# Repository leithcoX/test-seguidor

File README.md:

# Robot Seguidor de Línea

Test de seguidor de línea para competiciones.
Nombre pendiente.

## Estructura del proyecto
Boceto de la estructura del proyecto

```bash
.
├── placa_sensor
│   ├── kicad_sch
│   └── kicad_pcb
├── placa_seguidor
│   ├── kicad_sch
│   └── kicad_pcb
├── modelo
│   └── seguidor.FCStd
├── include
│   ├── file1.h
│   └── file2.h
├── src
│   ├── file1.ino
│   └── file2.ino
├── res
│   ├── datasheets.pdf
│   ├── images.png
│   └── referencias o links
└── README.md
```

## Requisitos
 - 20cm largo x 14cm de ancho x 10cm de alto
 - Area mínima de 23mm x 14mm. Visible. No pueden ser secciones de la batería.
 - No control remoto, o que solo de la orden de salida
 - Indicador luminoso (fijo o intermitente) que muestra cuando el robot inicia a correr.
 - Ruedas sin adherentes

## TODOs
 - ~~Rediseñar la placa de sensores (corregir errores) y mandar al lci~~
 - ~~Puente H~~
 - ~~Arduino Nano o ATmega328~~ y programarlo
 - ~~Comprar Placa Experimental~~
 - Elegir batería
 - Hacer un diagrama tal vez de como seguir el proyecto
 - ~~Hacér una bitácora~~ (subirla al repo?)
 - Agregar vista general del proyecto desde la página principal
 - ~~Agregar una lista de compras que puedan editar todos~~
 - Terminar de Soldar/limpiar modulo de sensores chequeando continuidad (Ciin lo hace el jueves)
 - Probar modulo se sensores con arduino (Armar código de prueba) 
 - 

## Artículos pendientes
 - 2 Capacitores 100nf (Puente H)
 - 10 x Diodos 1N4007  (Puente H)
 - 1 x Zócalo ZT16A (Zocalo 16 pines para puente H)

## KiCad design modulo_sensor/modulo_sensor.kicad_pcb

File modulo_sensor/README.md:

# Modulo de sensores

Este módulo se encarga de la lectura de la línea.

[comment]: Hacer_alguna_descripción_más

Vista previa de la PCB desde arriba

Vista previa de la PCB desde abajo

## TODOs
En orden de prioridad
- ~~Automatizar exportar los archivos de fabricación~~
- Hacer las pistas más grandes si es posible
- El script debe exportar a PDF ambos lados en la misma hoja conservando las dimensiones para imprimir el circuito.
- ~~Exportar a otros formatos (SVG, STEP, etc)~~
- Agregar alguna compatibilidad para Windows(?
- Agregar algun check para el momento de subir a Github
- Tal vez agregar algunas opciones para controlar el script(?
- Cambiar las rutas relativas con alguna variable de entorno(?

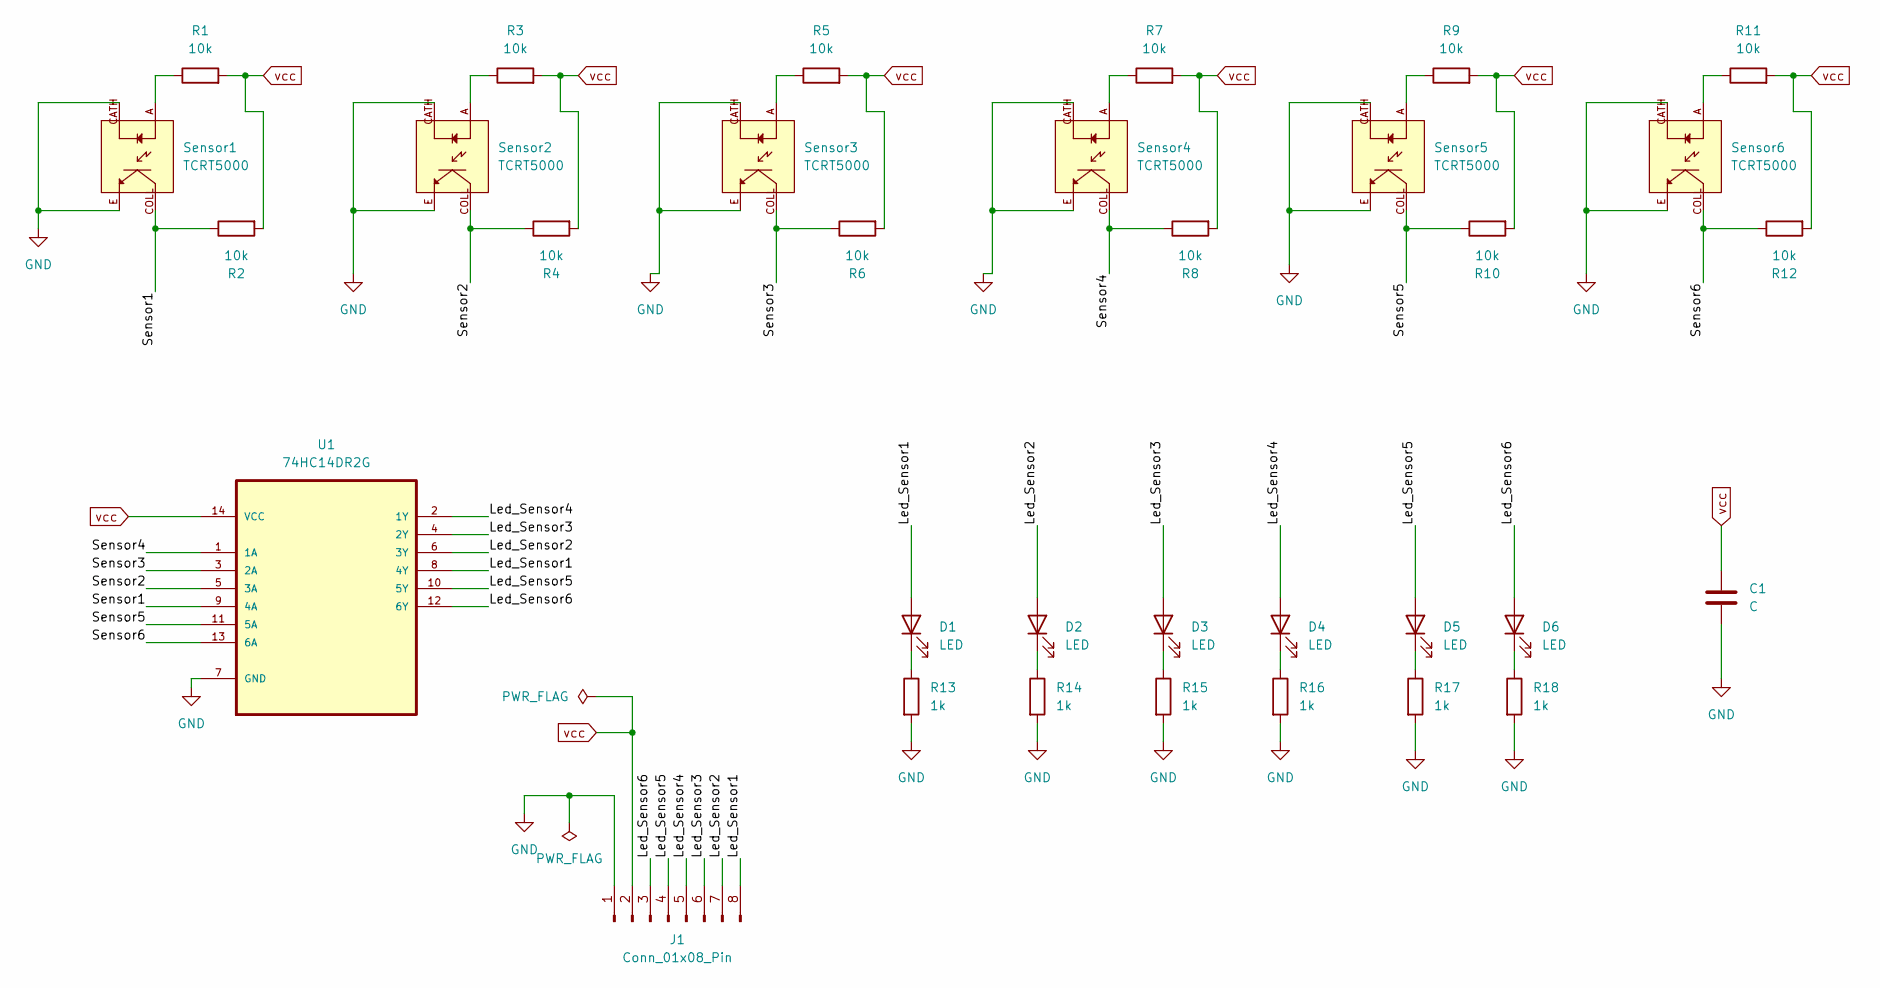
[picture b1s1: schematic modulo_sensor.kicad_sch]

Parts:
C1: C; C_Disc_D3.0mm_W1.6mm_P2.50mm
D1, D2, D3, D4, D5, D6: LED; LED_1206_3216Metric_Pad1.42x1.75mm_HandSolder
J1: Conn_01x08_Pin; PinHeader_1x08_P2.54mm_Horizontal
R1, R2, R3, R4, R5, R6, R7, R8, R9, R10, R11, R12: 10k; R_0805_2012Metric_Pad1.20x1.40mm_HandSolder
R13, R14, R15, R16, R17, R18: 1k; R_0805_2012Metric_Pad1.20x1.40mm_HandSolder
Sensor1, Sensor2, Sensor3, Sensor4, Sensor5, Sensor6: TCRT5000; OPTO_TCRT5000; PARTREV 1.7
U1: 74HC14DR2G; DIP-14_W7.62mm_Socket; MPN 74HC14DR2G

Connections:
/Led_Sensor1: D1.2 (A), J1.8, U1.8 (4Y)
/Led_Sensor2: D2.2 (A), J1.7, U1.6 (3Y)
/Led_Sensor3: D3.2 (A), J1.6, U1.4 (2Y)
/Led_Sensor4: D4.2 (A), J1.5, U1.2 (1Y)
/Led_Sensor5: D5.2 (A), J1.4, U1.10 (5Y)
/Led_Sensor6: D6.2 (A), J1.3, U1.12 (6Y)
/Sensor1: R2.1, Sensor1.COLL, U1.9 (4A)
/Sensor2: R4.1, Sensor2.COLL, U1.5 (3A)
/Sensor3: R6.1, Sensor3.COLL, U1.3 (2A)
/Sensor4: R8.1, Sensor4.COLL, U1.1 (1A)
/Sensor5: R10.1, Sensor5.COLL, U1.11 (5A)
/Sensor6: R12.1, Sensor6.COLL, U1.13 (6A)
GND: C1.2, J1.1, R13.2, R14.2, R15.2, R16.2, R17.2, R18.2, Sensor1.CATH, Sensor1.E, Sensor2.CATH, Sensor2.E, Sensor3.CATH, Sensor3.E, Sensor4.CATH, Sensor4.E, Sensor5.CATH, Sensor5.E, Sensor6.CATH, Sensor6.E, U1.7 (GND)
unnamed: D1.1 (K), R13.1
unnamed: D2.1 (K), R14.1
unnamed: D3.1 (K), R15.1
unnamed: D4.1 (K), R16.1
unnamed: D5.1 (K), R17.1
unnamed: D6.1 (K), R18.1
unnamed: R1.1, Sensor1.A
unnamed: R3.1, Sensor2.A
unnamed: R5.1, Sensor3.A
unnamed: R7.1, Sensor4.A
unnamed: R9.1, Sensor5.A
unnamed: R11.1, Sensor6.A
vcc: C1.1, J1.2, R1.2, R2.2, R3.2, R4.2, R5.2, R6.2, R7.2, R8.2, R9.2, R10.2, R11.2, R12.2, U1.14 (VCC)

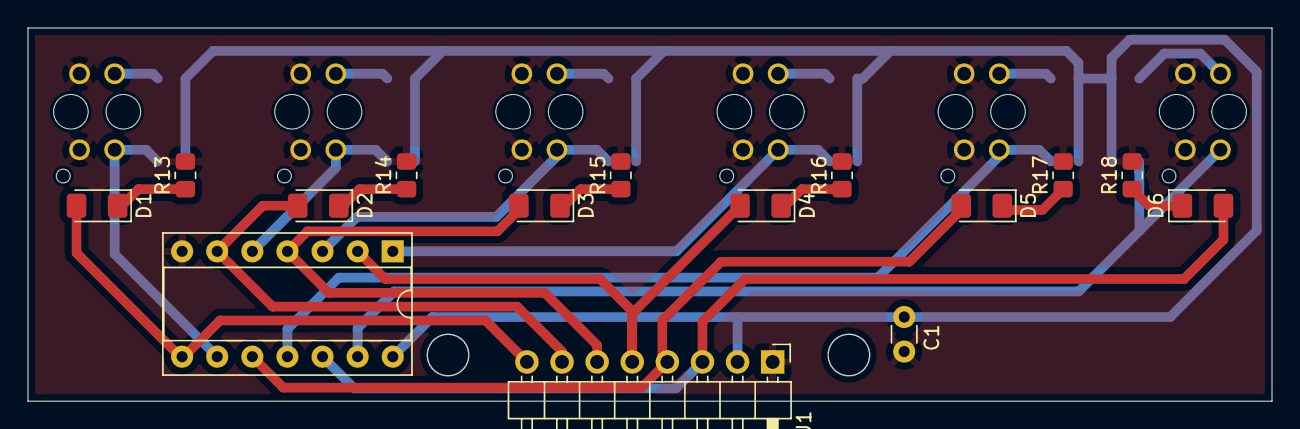
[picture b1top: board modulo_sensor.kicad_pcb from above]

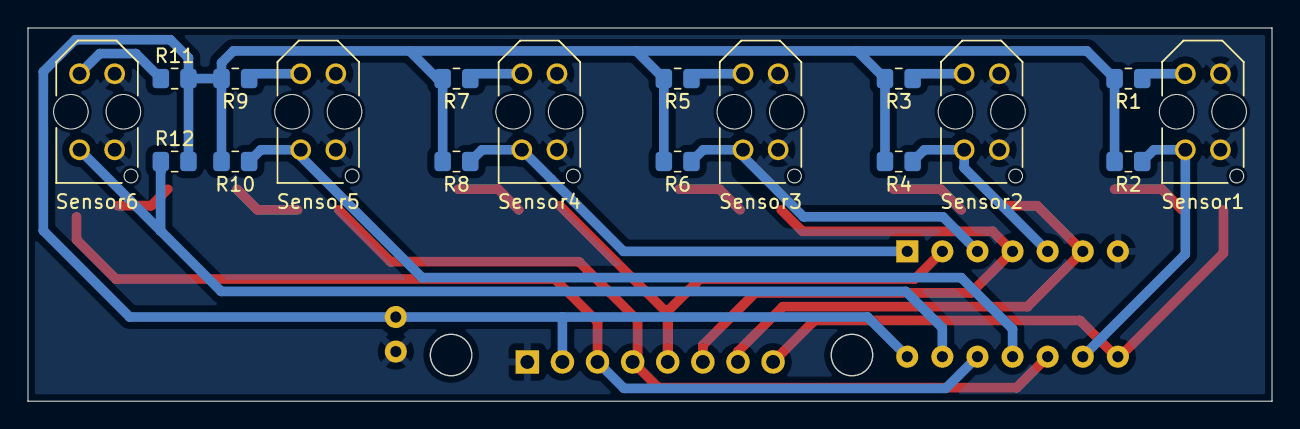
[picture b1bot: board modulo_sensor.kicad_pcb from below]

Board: 2 copper layers, 89.9 x 27.0 mm, 33 parts (18 on the bottom side), 26 nets.

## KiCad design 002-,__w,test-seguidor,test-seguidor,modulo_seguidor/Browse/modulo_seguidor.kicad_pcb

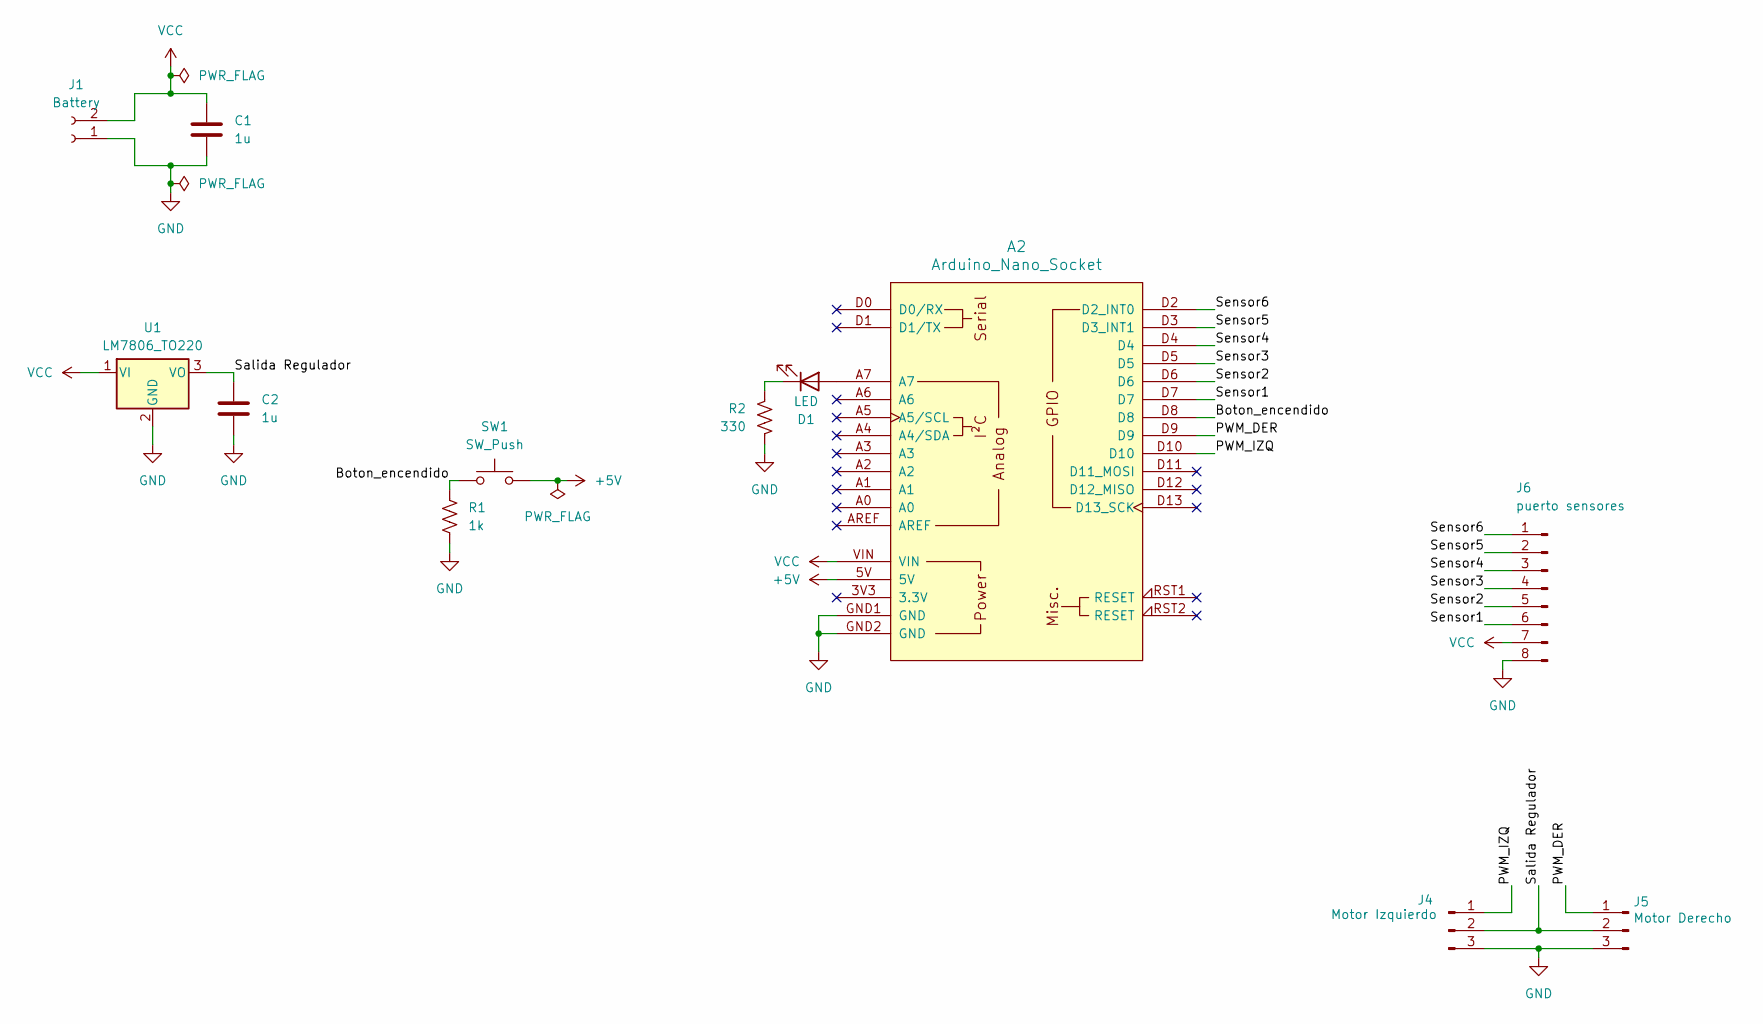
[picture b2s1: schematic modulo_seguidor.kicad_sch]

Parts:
A2: Arduino_Nano_Socket
C1, C2: 1u; C_Disc_D7.0mm_W2.5mm_P5.00mm
D1: LED; LED_D5.0mm
J1: Battery; Molex_KK-254_AE-6410-02A_1x02_P2.54mm_Vertical
J4: Motor Izquierdo; PinHeader_1x03_P2.54mm_Vertical
J5: Motor Derecho; PinHeader_1x03_P2.54mm_Vertical
J6: puerto sensores; PinHeader_1x08_P2.54mm_Horizontal
R1: 1k; R_Axial_DIN0411_L9.9mm_D3.6mm_P12.70mm_Horizontal
R2: 330; R_Axial_DIN0411_L9.9mm_D3.6mm_P12.70mm_Horizontal
SW1: SW_Push; SW_PUSH_6mm
U1: LM7806_TO220; TO-220-3_Vertical

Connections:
+5V: A2.5V, SW1.1
/Boton_encendido: A2.D8, R1.1, SW1.2
/PWM_DER: A2.D9, J5.1
/PWM_IZQ: A2.D10, J4.1
/Salida Regulador: C2.1, J4.2, J5.2, U1.3 (VO)
/Sensor1: A2.D7, J6.6
/Sensor2: A2.D6, J6.5
/Sensor3: A2.D5, J6.4
/Sensor4: A2.D4, J6.3
/Sensor5: A2.D3 (D3_INT1), J6.2
/Sensor6: A2.D2 (D2_INT0), J6.1
GND: A2.GND1 (GND), A2.GND2 (GND), C1.2, C2.2, J1.1, J4.3, J5.3, J6.8, R1.2, R2.2, U1.2 (GND)
unnamed: A2.A7, D1.2 (A)
unnamed: D1.1 (K), R2.1
VCC: A2.VIN, C1.1, J1.2, J6.7, U1.1 (VI)

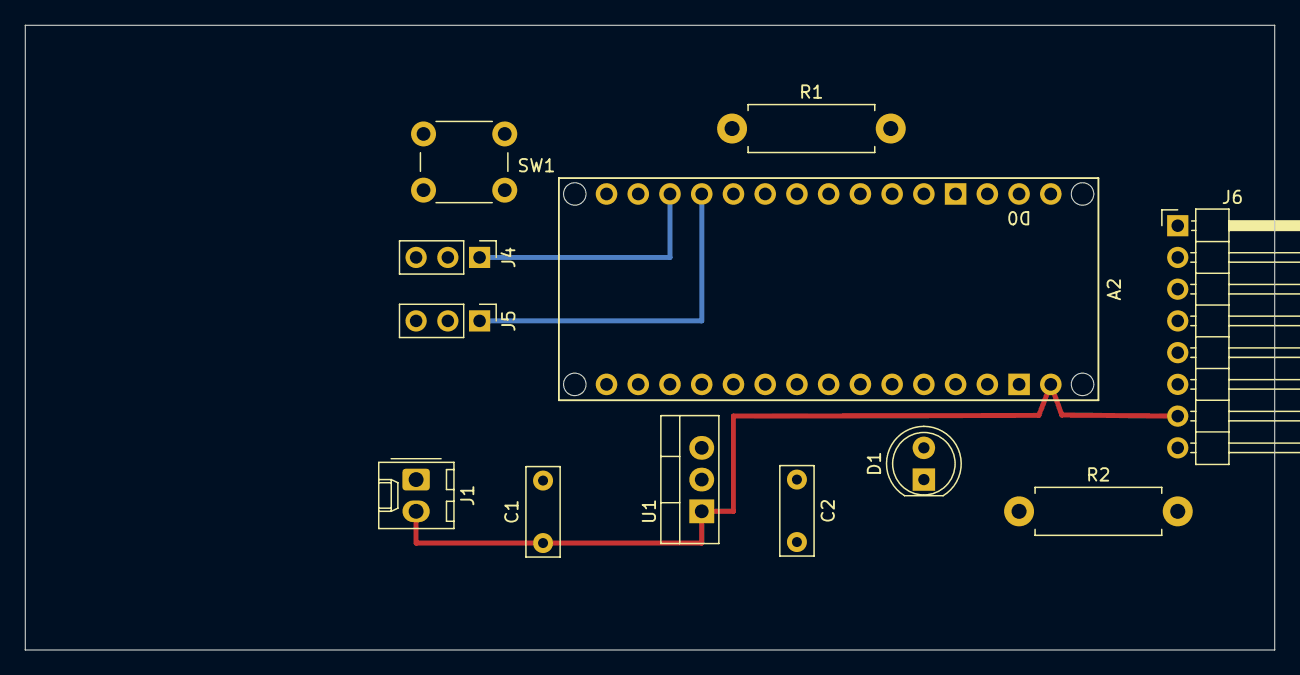
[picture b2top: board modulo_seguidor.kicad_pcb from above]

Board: 12 copper layers, 100.0 x 50.0 mm, 12 parts (0 on the bottom side), 15 nets.

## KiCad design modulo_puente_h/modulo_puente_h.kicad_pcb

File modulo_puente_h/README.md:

# Modulo Puente H

Este módulo se encarga de controlar los motores a partir de las entradas recibidas por sus pines.

Las pistas azules representan conexiones físicas cableadas por nosotros ya que el diseño no es posible en una placa simple faz.

## TODOs
 - [ ] Revisar las medidas de la placa
 - [ ] Hacer los agujeros para las medidas del modelo 3D
 - [ ] El regulador de tensión debería ir en este módulo?
 - [ ] Revisar las conexiones
 - [ ] Replantearse el diseño del puente h, ¿Qué tensión tienen los motores?

#### Nota

Considerar que se podría diseñar todo en la parte posterior y soldar los componentes del lado que no tiene cobre.

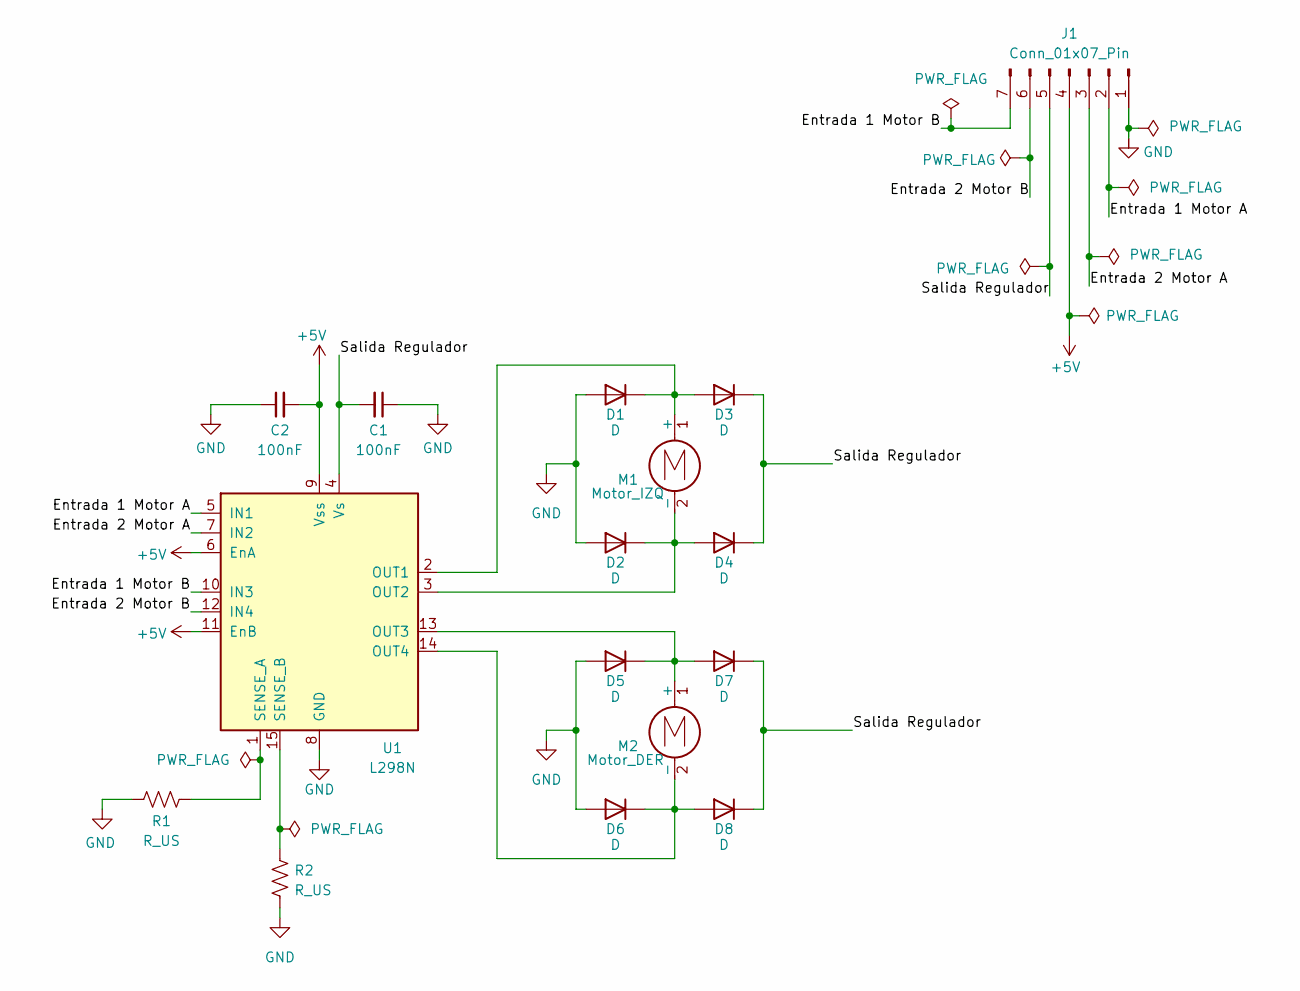
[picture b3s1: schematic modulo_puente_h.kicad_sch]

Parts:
C1, C2: 100nF; C_Disc_D7.0mm_W2.5mm_P5.00mm
D1, D2, D3, D4, D5, D6, D7, D8: D; D_DO-41_SOD81_P7.62mm_Horizontal
J1: Conn_01x07_Pin; PinHeader_1x07_P2.54mm_Vertical
M1: Motor_IZQ; R_Axial_DIN0207_L6.3mm_D2.5mm_P2.54mm_Vertical
M2: Motor_DER; R_Axial_DIN0207_L6.3mm_D2.5mm_P2.54mm_Vertical
R1, R2: R_US; R_0805_2012Metric_Pad1.20x1.40mm_HandSolder
U1: L298N; TO-220-15_P2.54x2.54mm_StaggerOdd_Lead4.58mm_Vertical

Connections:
+5V: C2.2, J1.4, U1.6 (EnA), U1.9 (Vss), U1.11 (EnB)
/Entrada 1 Motor A: J1.2, U1.5 (IN1)
/Entrada 1 Motor B: J1.7, U1.10 (IN3)
/Entrada 2 Motor A: J1.3, U1.7 (IN2)
/Entrada 2 Motor B: J1.6, U1.12 (IN4)
/Salida Regulador: C1.2, D3.1 (K), D4.1 (K), D7.1 (K), D8.1 (K), J1.5, U1.4 (Vs)
GND: C1.1, C2.1, D1.2 (A), D2.2 (A), D5.2 (A), D6.2 (A), J1.1, R1.2, R2.1, U1.8 (GND)
unnamed: D1.1 (K), D3.2 (A), M1.1 (+), U1.2 (OUT1)
unnamed: D2.1 (K), D4.2 (A), M1.2 (-), U1.3 (OUT2)
unnamed: D5.1 (K), D7.2 (A), M2.1 (+), U1.13 (OUT3)
unnamed: D6.1 (K), D8.2 (A), M2.2 (-), U1.14 (OUT4)
unnamed: R1.1, U1.1 (SENSE_A)
unnamed: R2.2, U1.15 (SENSE_B)

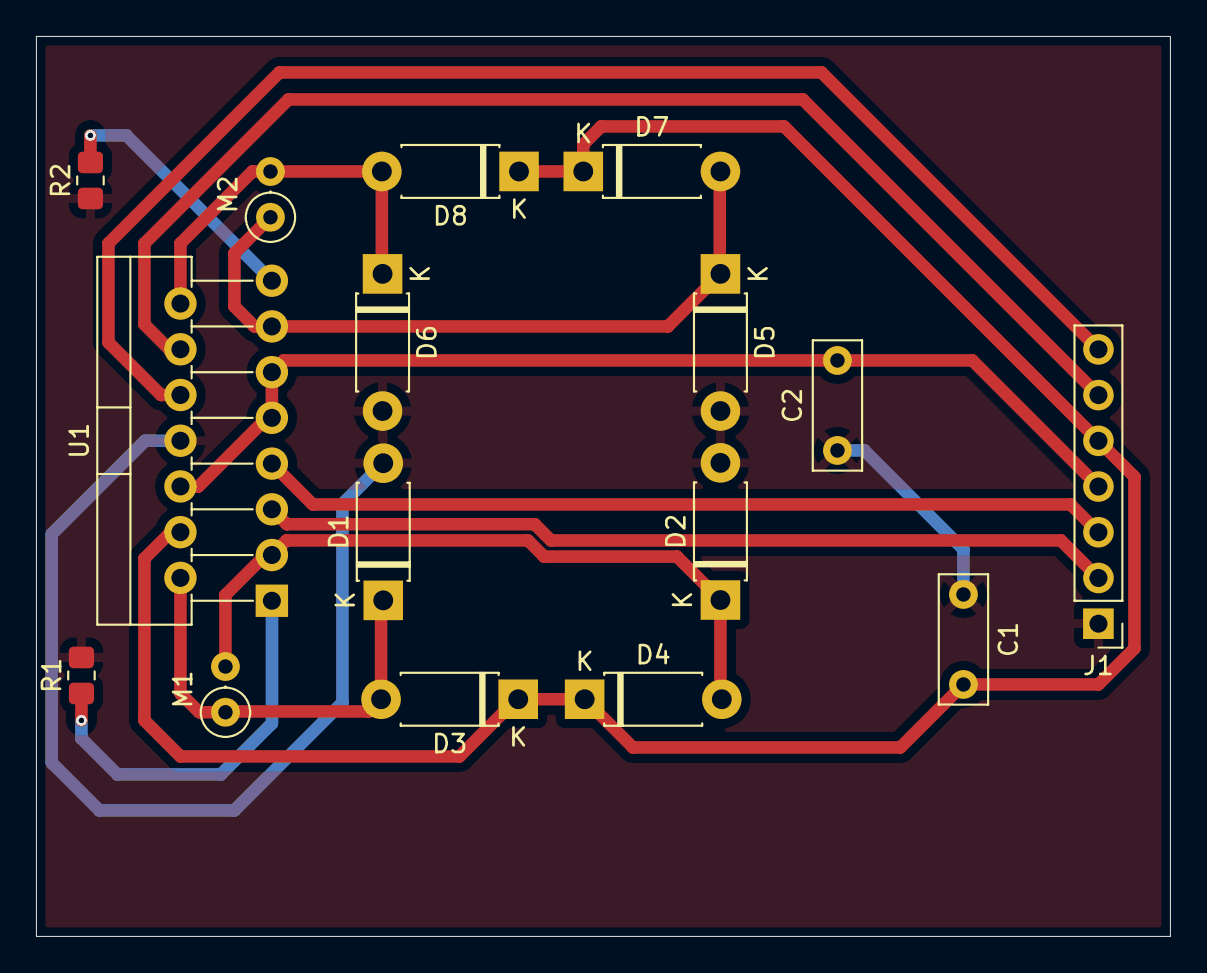
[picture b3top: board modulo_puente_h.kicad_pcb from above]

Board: 2 copper layers, 63.0 x 50.0 mm, 16 parts (0 on the bottom side), 13 nets.

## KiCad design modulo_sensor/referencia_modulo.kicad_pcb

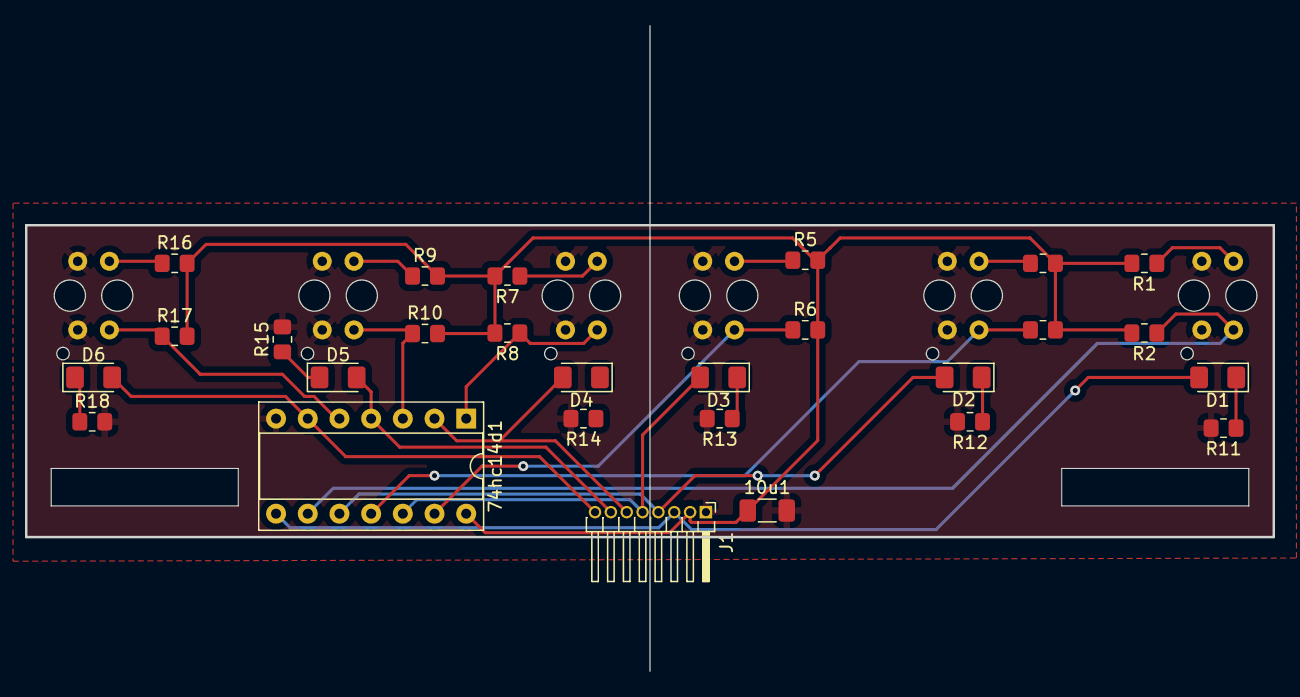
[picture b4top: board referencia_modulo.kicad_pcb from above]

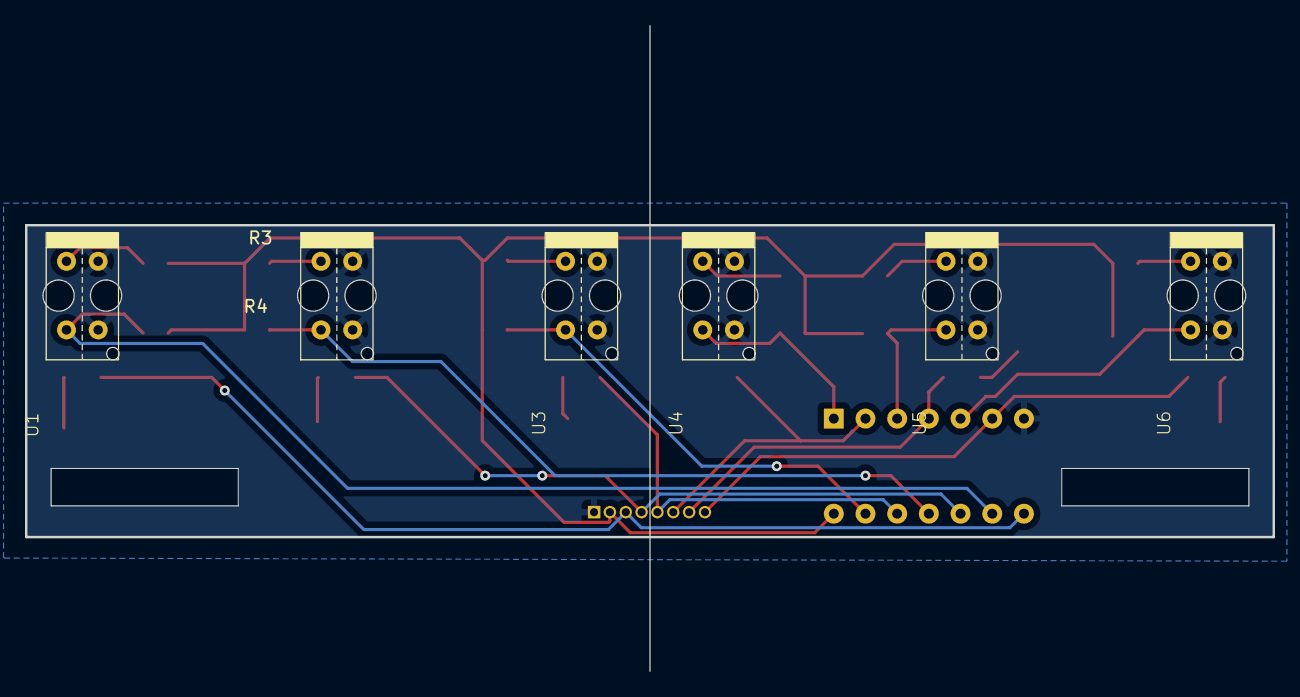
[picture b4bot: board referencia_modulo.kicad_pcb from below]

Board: 2 copper layers, 100.0 x 51.7 mm, 33 parts (6 on the bottom side), 26 nets.

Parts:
10u1: CAP; C_1206_3216Metric_Pad1.33x1.80mm_HandSolder
74hc14d1: A_14-LC-TT; DIP-14_W7.62mm_Socket
D1, D2, D3, D4, D5, D6: LED; LED_1206_3216Metric_Pad1.42x1.75mm_HandSolder
J1: Conn_01x08_Pin; PinHeader_1x08_P1.27mm_Horizontal
R1, R3, R5, R7, R9, R16: 220; R_0805_2012Metric_Pad1.20x1.40mm_HandSolder
R2, R4, R6, R8, R10, R17: 10k; R_0805_2012Metric_Pad1.20x1.40mm_HandSolder
R11, R12, R13, R14, R15, R18: 1k; R_0805_2012Metric_Pad1.20x1.40mm_HandSolder
U1, U2, U3, U4, U5, U6: TCMT4106; tcrt5000

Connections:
/sensor1: 74hc14d1.8, D1.2 (A), J1.3
/sensor1_unfiltered: 74hc14d1.9, R2.1, U1.16
/sensor2: 74hc14d1.10, D2.2 (A), J1.4
/sensor2_unfiltered: 74hc14d1.11, R4.1, U2.16
/sensor3: 74hc14d1.12, D3.2 (A), J1.5
/sensor3_unfiltered: 74hc14d1.13, R6.1, U3.16
/sensor4: 74hc14d1.2, D4.2 (A), J1.6
/sensor4_unfiltered: 74hc14d1.1, R8.1, U4.16
/sensor5: 74hc14d1.4, D5.2 (A), J1.7
/sensor5_unfiltered: 74hc14d1.3, R10.1, U5.16
/sensor6: 74hc14d1.6, D6.2 (A), J1.8
/sensor6_unfiltered: 74hc14d1.5, R17.1, U6.16
GND: 10u1.2, 74hc14d1.7, J1.1, R11.2, R12.2, R13.2, R14.2, R15.2, R18.2, U1.2, U1.15, U2.2, U2.15, U3.2, U3.15, U4.2, U4.15, U5.2, U5.15, U6.2, U6.15
unnamed: D1.1 (K), R11.1
unnamed: D2.1 (K), R12.1
unnamed: D3.1 (K), R13.1
unnamed: D4.1 (K), R14.1
unnamed: D5.1 (K), R15.1
unnamed: D6.1 (K), R18.1
unnamed: R1.1, U1.1
unnamed: R3.1, U2.1
unnamed: R5.1, U3.1
unnamed: R7.1, U4.1
unnamed: R9.1, U5.1
unnamed: R16.1, U6.1
VCC: 10u1.1, 74hc14d1.14, J1.2, R1.2, R2.2, R3.2, R4.2, R5.2, R6.2, R7.2, R8.2, R9.2, R10.2, R16.2, R17.2

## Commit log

2025-05-08 test commit
2025-05-09 feat: Add workflow
2025-05-09 Deploying to main from @ leithcoX/test-seguidor@514b852d081cf7de3d81e669fe0f0a6481729ef0 🚀
2025-05-09 Revert "Update main.yml"
    This reverts commit 5114412c30cf3efa088ca76868943fefebbf43f6.
2025-05-09 Revert "test commit"
    This reverts commit 514b852d081cf7de3d81e669fe0f0a6481729ef0.
2025-05-09 Reapply "Update main.yml"
    This reverts commit 3892fc5ccf7d4ef1b22bbb9e9d7fdde5756f8f6d.
2025-05-09 Revert "test commit"
    This reverts commit c76c6ea8ef0f57f14bd263cc8ad10acd8b36b6e4.
2025-05-09 Reapply "test commit"
    This reverts commit 001485671d3bcb7118b611520cc931e91d9a4268.
2025-05-09 Revert "Deploying to main from @ leithcoX/test-seguidor@514b852d081cf7de3d81e669fe0f0a6481729ef0 🚀"
    This reverts commit 73fc4e96f61ec003882416f7a758038d56a8601e.
